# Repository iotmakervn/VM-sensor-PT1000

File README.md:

# VM-sensor-PT1000

## Hardware

### Schematics

### PCB Layout

### 3D

### Gerber

[Download](./assets/gerber.zip)

### BOM 
| Id | Designator  | Package                              | Quantity | Designation                      |
|----|-------------|--------------------------------------|----------|----------------------------------|
| 1  | U1          | TO-263-5Lead                         | 1        | LM2595S-3.3                      |
| 2  | U2          | SOT-23-5                             | 1        | MCP601T                          |
| 3  | D1          | do214aa-g                            | 1        | SS34                             |
| 4  | D2          | LED-3MM                              | 1        | LED_Small                        |
| 5  | L1          | Choke_SMD_12x12mm_h8mm               | 1        | 47uH/RH127-470                   |
| 6  | C1          | c_elec_10x10.5 Aluminum              | 1        | 470uF/50v                        |
| 7  | C3          | Tantalum_Case-D_EIA-7343-31_Hand     | 1        | 330uF/16V                        |
| 8  | C4,C5,C6    | C_0805                               | 3        | 10uF/16v                         |
| 9  | C2          | C_0805                               | 1        | 10uF/50v                         |
| 10 | R1,R4       | R_0805                               | 2        | 3.3K/1%                          |
| 11 | R2          | R_0805                               | 1        | 100R/1%                          |
| 12 | R3,R6       | R_0805                               | 2        | 16.9K/1%                         |
| 13 | R5,R7       | R_0805                               | 2        | 1M/1%                            |
| 14 | R8          | R_0805                               | 1        | 1K/1%                            |
| 15 | R9          | R_0805                               | 1        | 100R                             |
| 16 | P3          | Domino-PT100.pretty                  | 1        | 4P-3.81 Pluggable Terminal Block |
| 17 | P2,P5,P6,P7 | Pin_Header_Straight_1x01_Pitch2.54mm | 4        | Male header, Pitch: 2.54MM       |
| 18 | P4,P1       | s2b-ph-kl                            | 2        | WB2F-L40P2.54                    |

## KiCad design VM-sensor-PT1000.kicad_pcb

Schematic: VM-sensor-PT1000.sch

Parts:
C1, C2: 10uF/25v; C_0805
C3, C4: 10uF; C_0805
D1: LED_Small; LED-3MM
P1: PT100; Domino-PT100.pretty
P2: ADC; s2b-ph-kl
P3: PWR; s2b-ph-kl
R1, R4: 3.3K/1%; R_0805
R2, R9: 100R/1%; R_0805
R3, R6: 16.9K/1%; R_0805
R5, R7: 1M/1%; R_0805
R8: 1K/1%; R_0805
U1: AMS1117; SOT-223
U2: MCP601T; SOT-23-5

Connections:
+3V3: C2.1, C3.1, R1.1, R4.1, R9.2, U1.2 (Vout), U2.5 (V+)
/ADC: C4.1, P2.1, R8.1
/Blue: R4.2, R6.2; also elsewhere on the board
GND: C1.2, C2.2, C3.2, C4.2, D1.1, P2.2, P3.2, R2.2, R7.1, U1.1 (GND/ADJ), U2.2 (V-); also elsewhere on the board
unnamed: D1.2, R9.1
unnamed: R1.2, R2.1, R3.2
unnamed: R3.1, R5.1, U2.4 (-)
unnamed: R5.2, R8.2, U2.1
unnamed: R6.1, R7.2, U2.3 (+)
VCC: C1.1, P3.1, U1.3 (Vin)

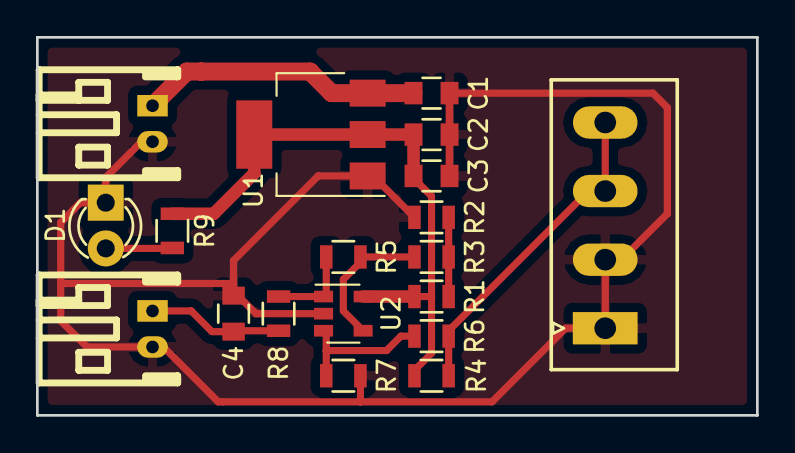
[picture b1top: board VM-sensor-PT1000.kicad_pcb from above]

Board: 2 copper layers, 40.0 x 21.0 mm, 19 parts (0 on the bottom side), 10 nets.

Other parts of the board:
PT100: PT100; Domino-PT100.pretty

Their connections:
/Blue: PT100.3, PT100.4; also elsewhere on the board
GND: PT100.1, PT100.2; also elsewhere on the board

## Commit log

2016-12-24 add schematic & PCB
2016-12-26 change component 0603 to 0805 & header
2016-12-26 Completed PCB
2016-12-26 remove file
2016-12-26 add gitignore file
2016-12-26 add assets folder
2017-01-06 Fix value resistor R3,R6, R7, R5 & symbol R2
2017-01-06 add led PWR & change header ADC
2017-01-07 completed new PCB design
2017-01-07 modify README file
2017-01-07 fix image PCB
2017-01-10 Final PCB
2017-01-10 remove lib AMS1117
